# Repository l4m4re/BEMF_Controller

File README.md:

# BEMF Controller

The Back EMF Controller is an experimental evolution of the successful [EasyController3](https://github.com/pgrady3/EasyController3). 

This version incorporates an asymmetric bridge topology, which allows for capturing and reusing the energy from the motor's back EMF, which is normally wasted because of the use of freewheeling diodes.

This allows for a more efficient controller, and potentially a longer range for battery-powered applications, as explained on [Wikipedia](https://en.wikipedia.org/wiki/Switched_reluctance_motor#Power_circuitry):

> The phases in an asymmetric bridge converter correspond to the motor phases. If both of the power switches on either side of the phase are turned on, then that corresponding phase is actuated. Once the current has risen above the set value, the switch turns off. The energy now stored within the winding maintains the current in the same direction, the so-called back EMF (BEMF). This BEMF is fed back through the diodes to the capacitor for re-use, thus improving efficiency.

In addition to this, the capacitor that is used to store the energy from the back EMF is implemented in a bank of 4 capacitors, which are switched between series (BEMF capture) and parallel (coil energizing) by means of a couple of diodes:

[Spice simulations](http://tuks.nl/wiki/index.php/Main/BEMFRecoveryCircuit) have shown that this way the time needed to collapse the magnetic field in the motor is significantly reduced, which might help to reduce rotor drag and thus further improve the efficiency of the controller:

At this moment, all of this is still a work in progress, and the controller is still in the design phase. 

## Schematic

At this moment, the schematic is being developed using KiCad, and can be found in the `kicad` folder. The schematic is still a work in progress, but the current version can be found [here](/kicad/BEMF_controller.pdf).

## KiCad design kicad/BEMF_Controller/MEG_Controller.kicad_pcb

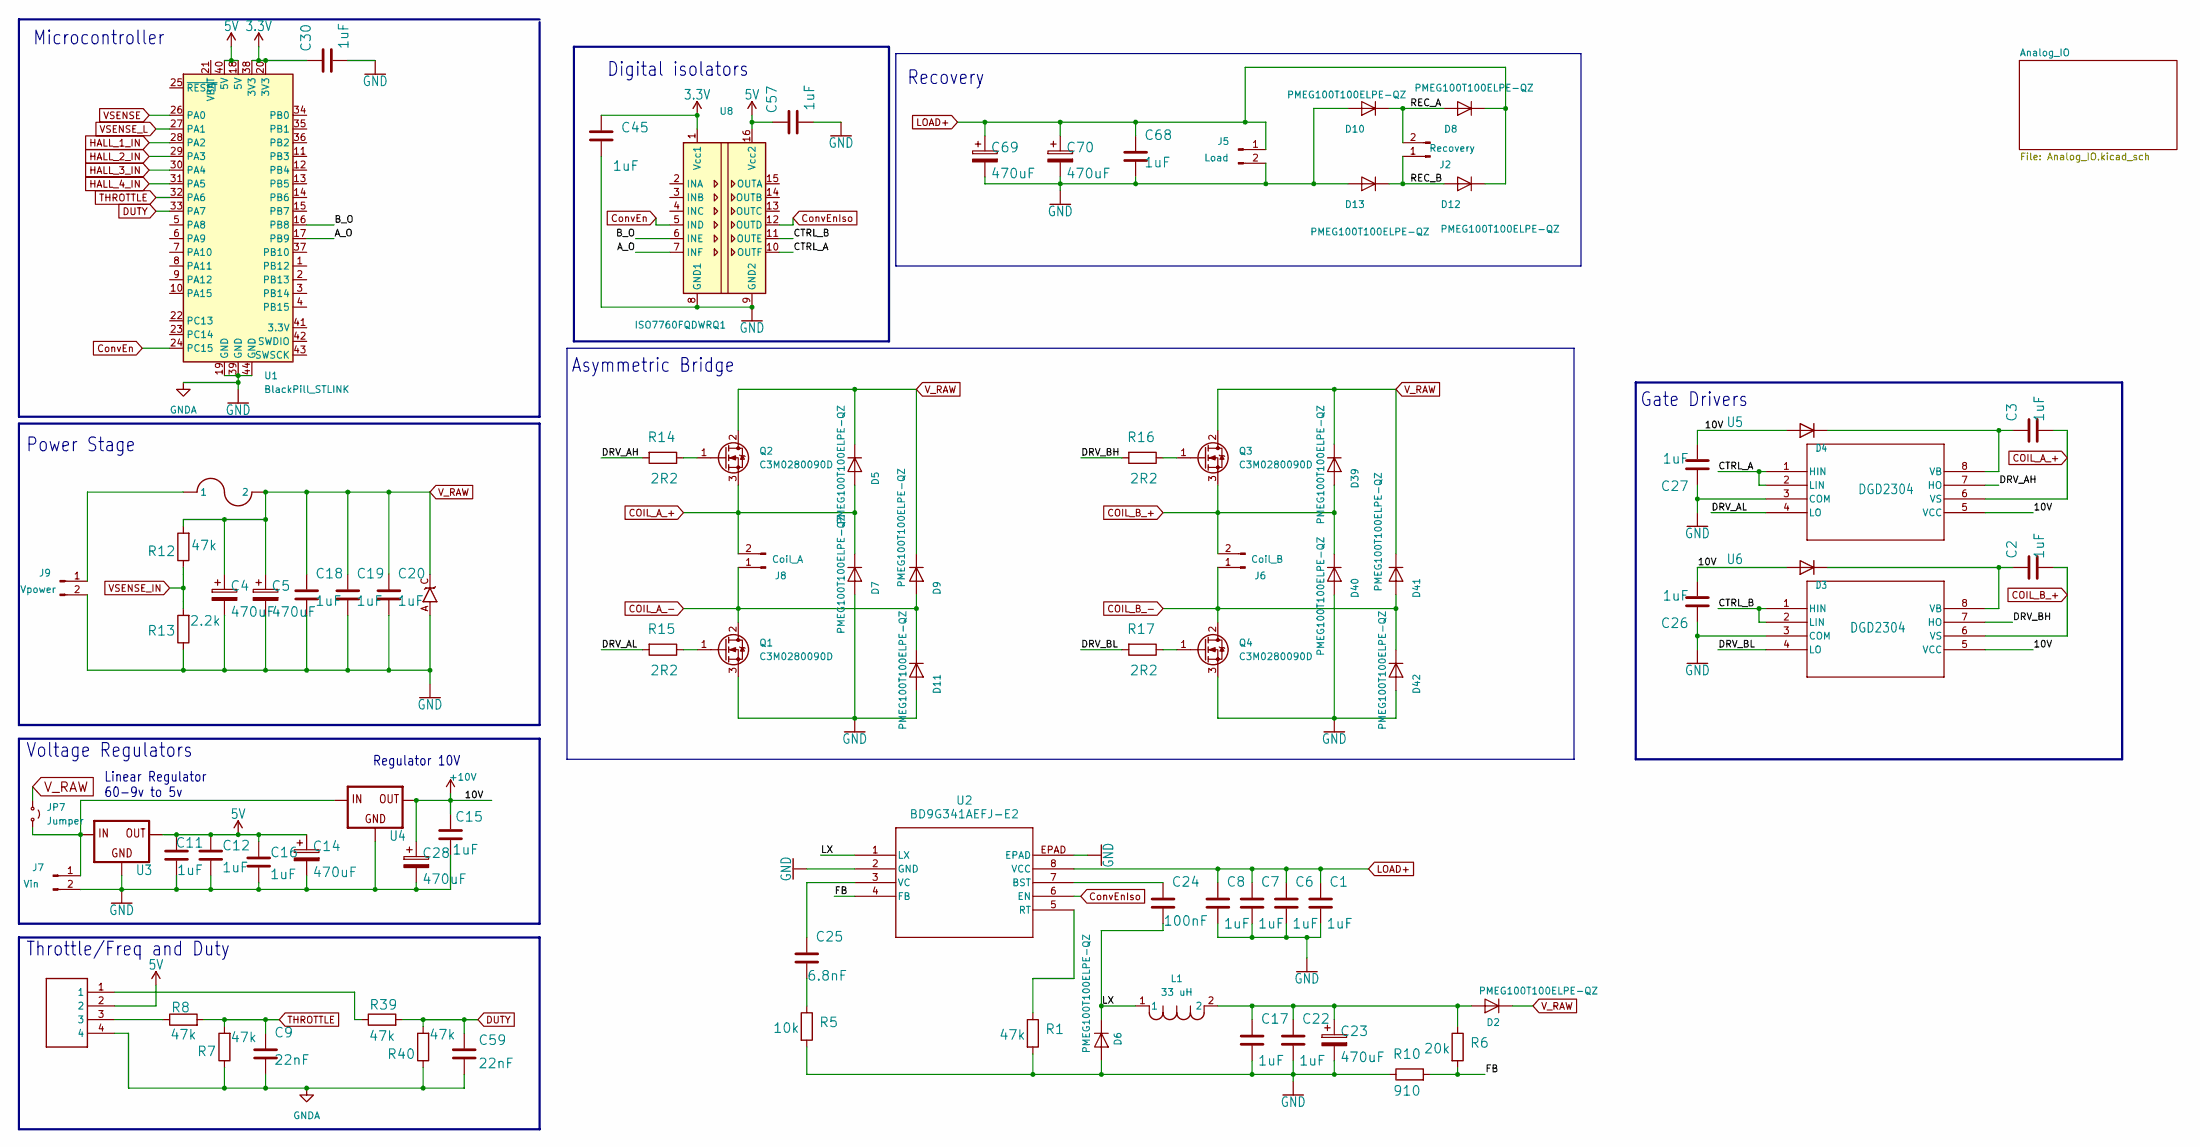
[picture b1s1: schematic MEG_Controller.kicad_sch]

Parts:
C1, C2, C3, C6, C7, C8, C11, C12, C15, C16, C17, C18, C19, C20, C22, C26, C27, C30, C45, C57, C68: 1uF; C_1812_4532Metric
C4, C5, C14, C23, C28, C69, C70: 470uF; CP_Radial_D10.0mm_P5.00mm
C9, C59: 22nF; C_0805_2012Metric
C24: 100nF; C_0805_2012Metric
C25: 6.8nF; C_0805_2012Metric
D1: TVS_UNIDO-214AC; DO-214AC
D2, D5, D6, D7, D8, D9, D10, D11, D12, D13, D39, D40, D41, D42: PMEG100T100ELPE-QZ; Nexperia_CFP15_SOT-1289
D3, D4: SMD-DIODE-100V-200MA(SOD-123); D_SOD-123
J1: HEADER4VALULOK; TerminalBlock_Phoenix_MKDS-1,5-4-5.08_1x04_P5.08mm_Horizont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
J2: Recovery; TerminalBlock_Phoenix_MKDS-1,5-2-5.08_1x02_P5.08mm_Horizont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
J3: FUSE; AUTO_FUSE
J5: Load; TerminalBlock_Phoenix_MKDS-1,5-2-5.08_1x02_P5.08mm_Horizont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
J6: Coil_B; TerminalBlock_Phoenix_MKDS-1,5-2-5.08_1x02_P5.08mm_Horizont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
J7: Vin; TerminalBlock_Phoenix_MKDS-1,5-2-5.08_1x02_P5.08mm_Horizont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
J8: Coil_A; TerminalBlock_Phoenix_MKDS-1,5-2-5.08_1x02_P5.08mm_Horizont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
J9: Vpower; TerminalBlock_Phoenix_MKDS-1,5-2-5.08_1x02_P5.08mm_Horizont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
JP7: Jumper; SolderJumper-2_P1.3mm_Open_RoundedPad1.0x1.5mm
L1: 33 uH; IND_BOURNS_SRN1060
Q1, Q2, Q3, Q4: C3M0280090D; TO-247-3_Vertical
R1, R7, R8, R12, R39, R40: 47k; R_1206_3216Metric
R5: 10k; R_1206_3216Metric
R6: 20k; R_1206_3216Metric
R10: 910; R_1206_3216Metric
R13: 2.2k; R_1206_3216Metric
R14, R15, R16, R17: 2R2; R_1206_3216Metric
U1: BlackPill_STLINK
U2: BD9G341AEFJ-E2; HTSOP-J8_ROM
U3: V_REG_7805; V78W_BACKWARDS
U4: V_REG_7810; V78W_BACKWARDS
U5, U6: DGD2304; SOICN-8_LTF
U8: ISO7760FQDWRQ1; SOIC-16W_7.5x10.3mm_P1.27mm

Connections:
3.3V: C30.1, C45.1, U1.20 (3V3), U1.38 (3V3), U8.1 (Vcc1); also elsewhere on the board
5V: C11.1, C12.1, C14.1, C16.1, C57.1, J1.2, U1.18 (5V), U1.40 (5V), U3.OUT, U8.16 (Vcc2); also elsewhere on the board
+10V: C15.1, C26.2, C27.2, C28.1, D3.2 (A), D4.2 (A), U4.OUT, U5.5 (VCC), U6.5 (VCC)
/A_O: U1.17 (PB9), U8.7 (INF)
/B_O: U1.16 (PB8), U8.6 (INE)
/CTRL_A: U5.1 (HIN), U5.2 (LIN), U8.10 (OUTF)
/CTRL_B: U6.1 (HIN), U6.2 (LIN), U8.11 (OUTE)
/DRV_AH: R14.2, U5.7 (HO)
/DRV_AL: R15.2, U5.4 (LO)
/DRV_BH: R16.2, U6.7 (HO)
/DRV_BL: R17.2, U6.4 (LO)
/FB: R6.2, R10.2, U2.4 (FB)
/LX: C24.2, D6.1 (A), D6.2 (A), L1.1, U2.1 (LX)
/REC_A: D8.3 (K), D10.1 (A), D10.2 (A), J2.2
/REC_B: D12.3 (K), D13.1 (A), D13.2 (A), J2.1
COIL_A_+: C3.2, D5.3 (K), D7.1 (A), D7.2 (A), J8.2, Q2.3 (S), U5.6 (VS)
COIL_A_-: D9.3 (K), D11.1 (A), D11.2 (A), J8.1, Q1.2 (D)
COIL_B_+: C2.2, D39.3 (K), D40.1 (A), D40.2 (A), J6.2, Q3.3 (S), U6.6 (VS)
COIL_B_-: D41.3 (K), D42.1 (A), D42.2 (A), J6.1, Q4.2 (D)
ConvEn: U1.24 (PC15), U8.5 (IND)
ConvEnIso: U2.6 (EN), U8.12 (OUTD)
DUTY: C59.1, R39.2, R40.2, U1.33 (PA7)
GND: C1.2, C4.2, C5.2, C6.2, C7.2, C8.2, C9.2, C11.2, C12.2, C14.2, C15.2, C16.2, C17.2, C18.2, C19.2, C20.2, C22.2, C23.2, C26.1, C27.1, C28.2, C30.2, C45.2, C57.2, C59.2, C68.2, C69.2, C70.2, D1.A, D6.3 (K), D7.3 (K), D10.3 (K), D11.3 (K), D13.3 (K), D40.3 (K), D42.3 (K), J1.4, J5.2, J7.2, J9.2, Q1.3 (S), Q4.3 (S), R1.2, R5.2, R7.1, R10.1, R13.1, R40.1, U1.19 (GND), U1.39 (GND), U1.44 (GND), U2.2 (GND), U2.EPAD, U3.GND, U4.GND, U5.3 (COM), U6.3 (COM), U8.8 (GND1), U8.9 (GND2); also elsewhere on the board
HALL_1_IN: U1.28 (PA2); also elsewhere on the board
HALL_2_IN: U1.29 (PA3); also elsewhere on the board
HALL_3_IN: U1.30 (PA4); also elsewhere on the board
HALL_4_IN: U1.31 (PA5); also elsewhere on the board
LOAD+: C1.1, C6.1, C7.1, C8.1, C68.1, C69.1, C70.1, D8.1 (A), D8.2 (A), D12.1 (A), D12.2 (A), J5.1, U2.8 (VCC); also elsewhere on the board
unnamed: C25.2, R5.1
unnamed: C17.1, C22.1, C23.1, D2.3 (K), L1.2, R6.1
unnamed: C2.1, D3.1 (K), U6.8 (VB)
unnamed: C3.1, D4.1 (K), U5.8 (VB)
unnamed: J1.1, R39.1
unnamed: J1.3, R8.1
unnamed: J7.1, JP7.2 (B), U3.IN, U4.IN
unnamed: J3.1A (1), J3.1B (1), J9.1
unnamed: Q1.1 (G), R15.1
unnamed: Q2.1 (G), R14.1
unnamed: Q3.1 (G), R16.1
unnamed: Q4.1 (G), R17.1
unnamed: C24.1, U2.7 (BST)
unnamed: R1.1, U2.5 (RT)
unnamed: C25.1, U2.3 (VC)
THROTTLE: C9.1, R7.2, R8.2, U1.32 (PA6)
VSENSE: U1.26 (PA0); also elsewhere on the board
VSENSE_IN: R12.1, R13.2; also elsewhere on the board
VSENSE_L: U1.27 (PA1); also elsewhere on the board
V_RAW: C4.1, C5.1, C18.1, C19.1, C20.1, D1.C, D2.1 (A), D2.2 (A), D5.1 (A), D5.2 (A), D9.1 (A), D9.2 (A), D39.1 (A), D39.2 (A), D41.1 (A), D41.2 (A), J3.2A (2), J3.2B (2), JP7.1 (A), Q2.2 (D), Q3.2 (D), R12.2

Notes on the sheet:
Digital isolators
Power Stage
Throttle/Freq and Duty
Microcontroller
Regulator 10V
Linear Regulator 60-9v to 5v
Voltage Regulators
Gate Drivers
Recovery
Asymmetric Bridge

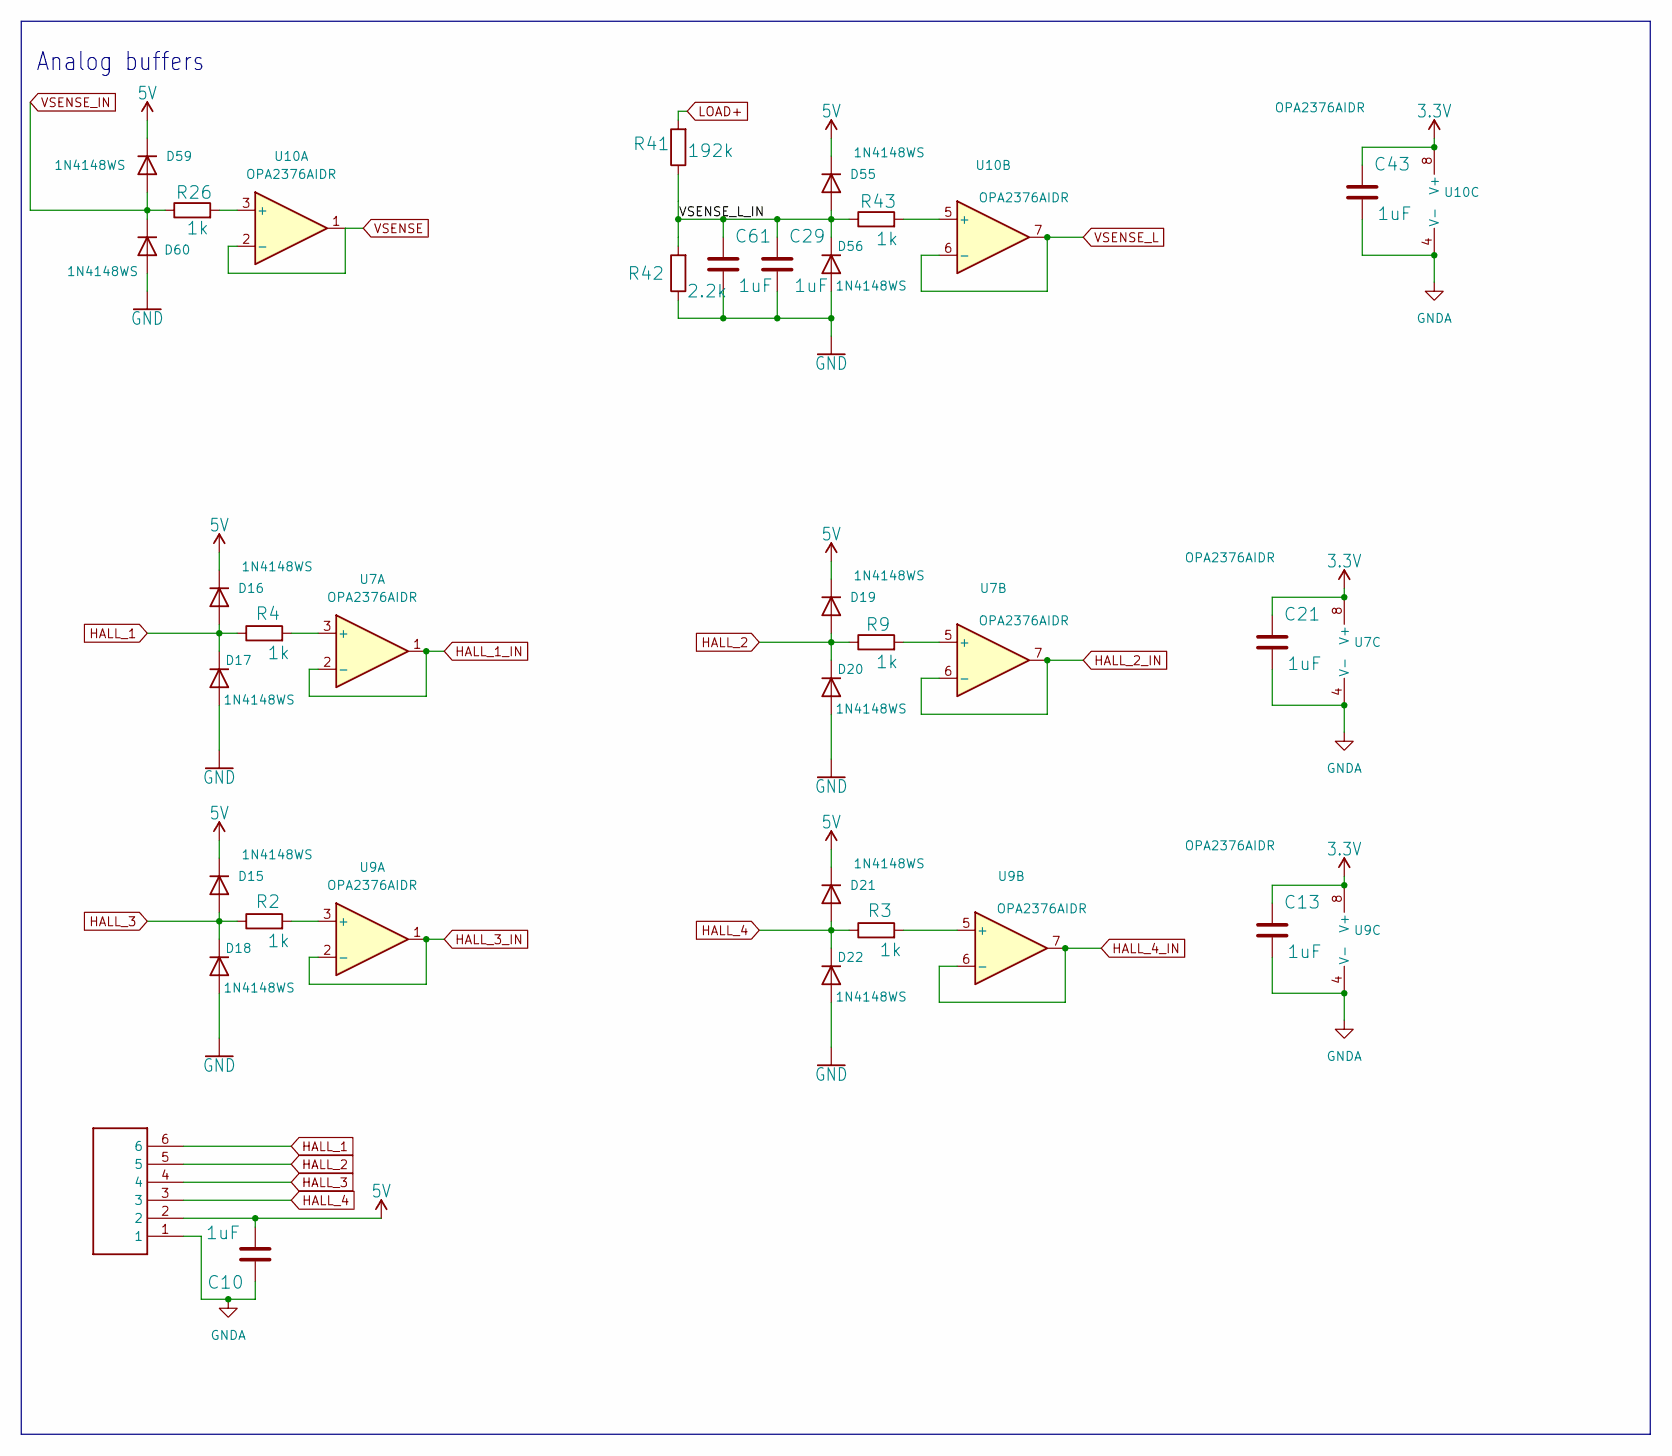
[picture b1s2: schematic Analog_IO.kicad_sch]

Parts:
C10, C13, C21, C29, C43, C61: 1uF; C_1812_4532Metric
D15, D16, D17, D18, D19, D20, D21, D22, D55, D56, D59, D60: 1N4148WS; D_SOD-323
J4: HEADER6; TerminalBlock_Phoenix_MKDS-1,5-6_1x06_P5.00mm_Horizontal
R2, R3, R4, R9, R26, R43: 1k; R_1206_3216Metric
R41: 192k; R_1206_3216Metric
R42: 2.2k; R_1206_3216Metric
U7, U9, U10: OPA2376AIDR; D8

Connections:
3.3V: C13.1, C21.1, C43.1, U7.8 (V+), U9.8 (V+), U10.8 (V+); also elsewhere on the board
5V: C10.2, D15.1 (K), D16.1 (K), D19.1 (K), D21.1 (K), D55.1 (K), D59.1 (K), J4.2; also elsewhere on the board
/Analog_IO/VSENSE_L_IN: C29.1, C61.1, D55.2 (A), D56.1 (K), R41.1, R42.2, R43.1
GND: C10.1, C13.2, C21.2, C29.2, C43.2, C61.2, D17.2 (A), D18.2 (A), D20.2 (A), D22.2 (A), D56.2 (A), D60.2 (A), J4.1, R42.1, U7.4 (V-), U9.4 (V-), U10.4 (V-); also elsewhere on the board
HALL_1: D16.2 (A), D17.1 (K), J4.6, R4.1
HALL_1_IN: U7.1, U7.2 (-); also elsewhere on the board
HALL_2: D19.2 (A), D20.1 (K), J4.5, R9.1
HALL_2_IN: U7.6 (-), U7.7; also elsewhere on the board
HALL_3: D15.2 (A), D18.1 (K), J4.4, R2.1
HALL_3_IN: U9.1, U9.2 (-); also elsewhere on the board
HALL_4: D21.2 (A), D22.1 (K), J4.3, R3.1
HALL_4_IN: U9.6 (-), U9.7; also elsewhere on the board
LOAD+: R41.2; also elsewhere on the board
unnamed: R4.2, U7.3 (+)
unnamed: R9.2, U7.5 (+)
unnamed: R2.2, U9.3 (+)
unnamed: R3.2, U9.5 (+)
unnamed: R26.2, U10.3 (+)
unnamed: R43.2, U10.5 (+)
VSENSE: U10.1, U10.2 (-); also elsewhere on the board
VSENSE_IN: D59.2 (A), D60.1 (K), R26.1; also elsewhere on the board
VSENSE_L: U10.6 (-), U10.7; also elsewhere on the board

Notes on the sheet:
Analog buffers

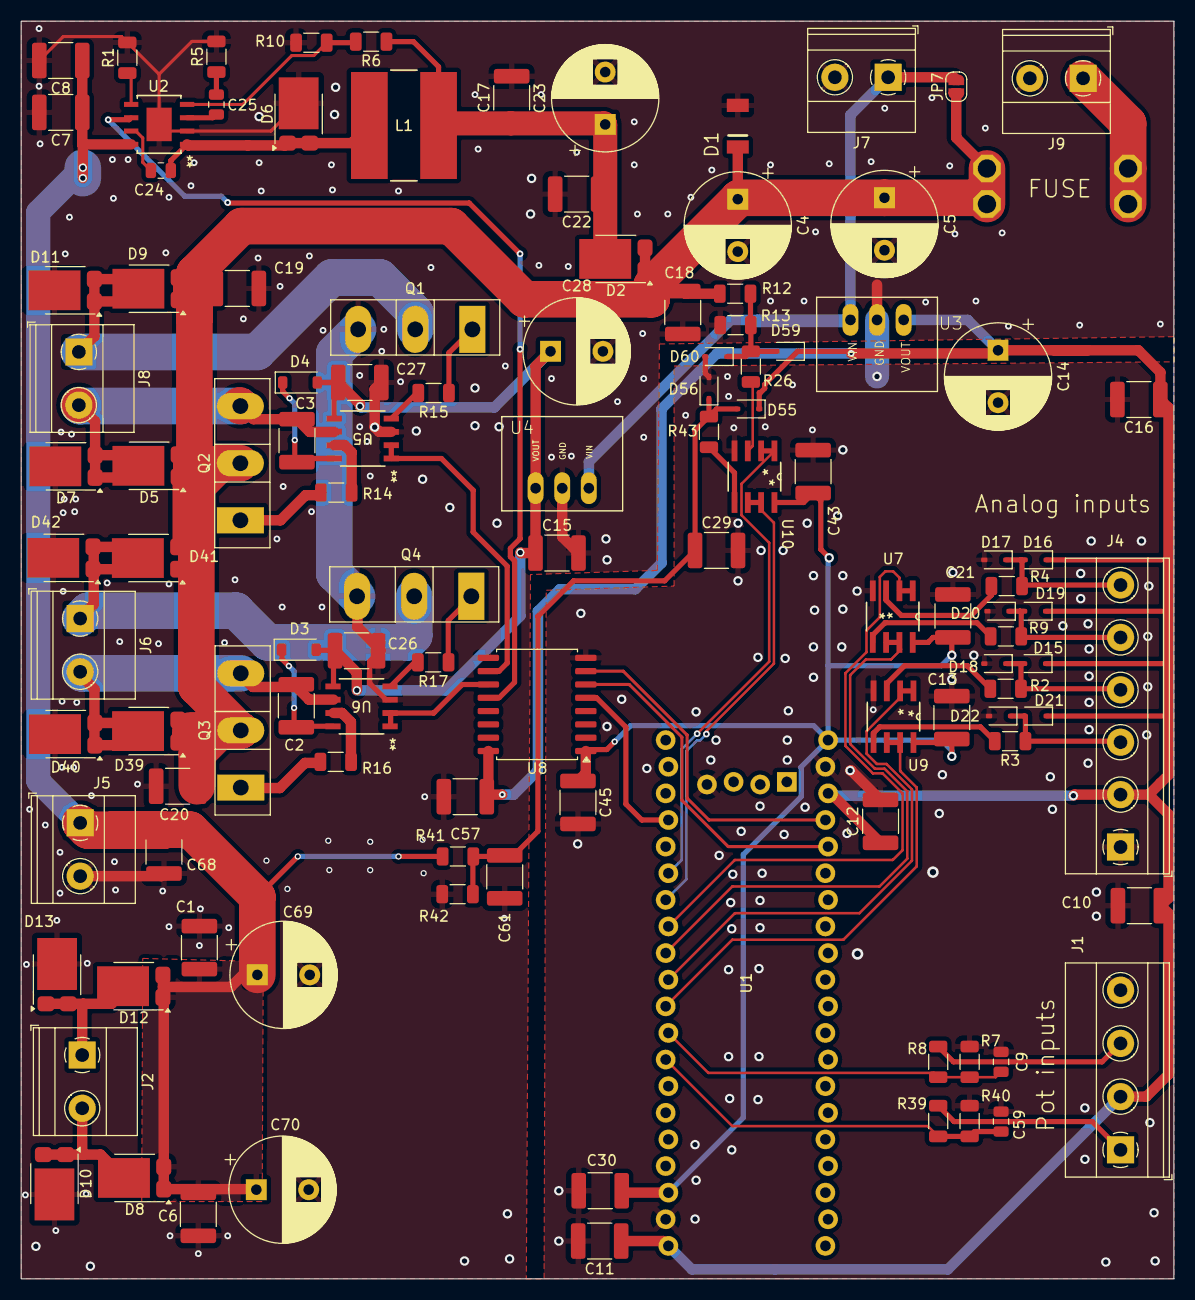
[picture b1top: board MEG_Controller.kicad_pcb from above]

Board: 2 copper layers, 110.0 x 120.0 mm, 114 parts (0 on the bottom side), 59 nets.

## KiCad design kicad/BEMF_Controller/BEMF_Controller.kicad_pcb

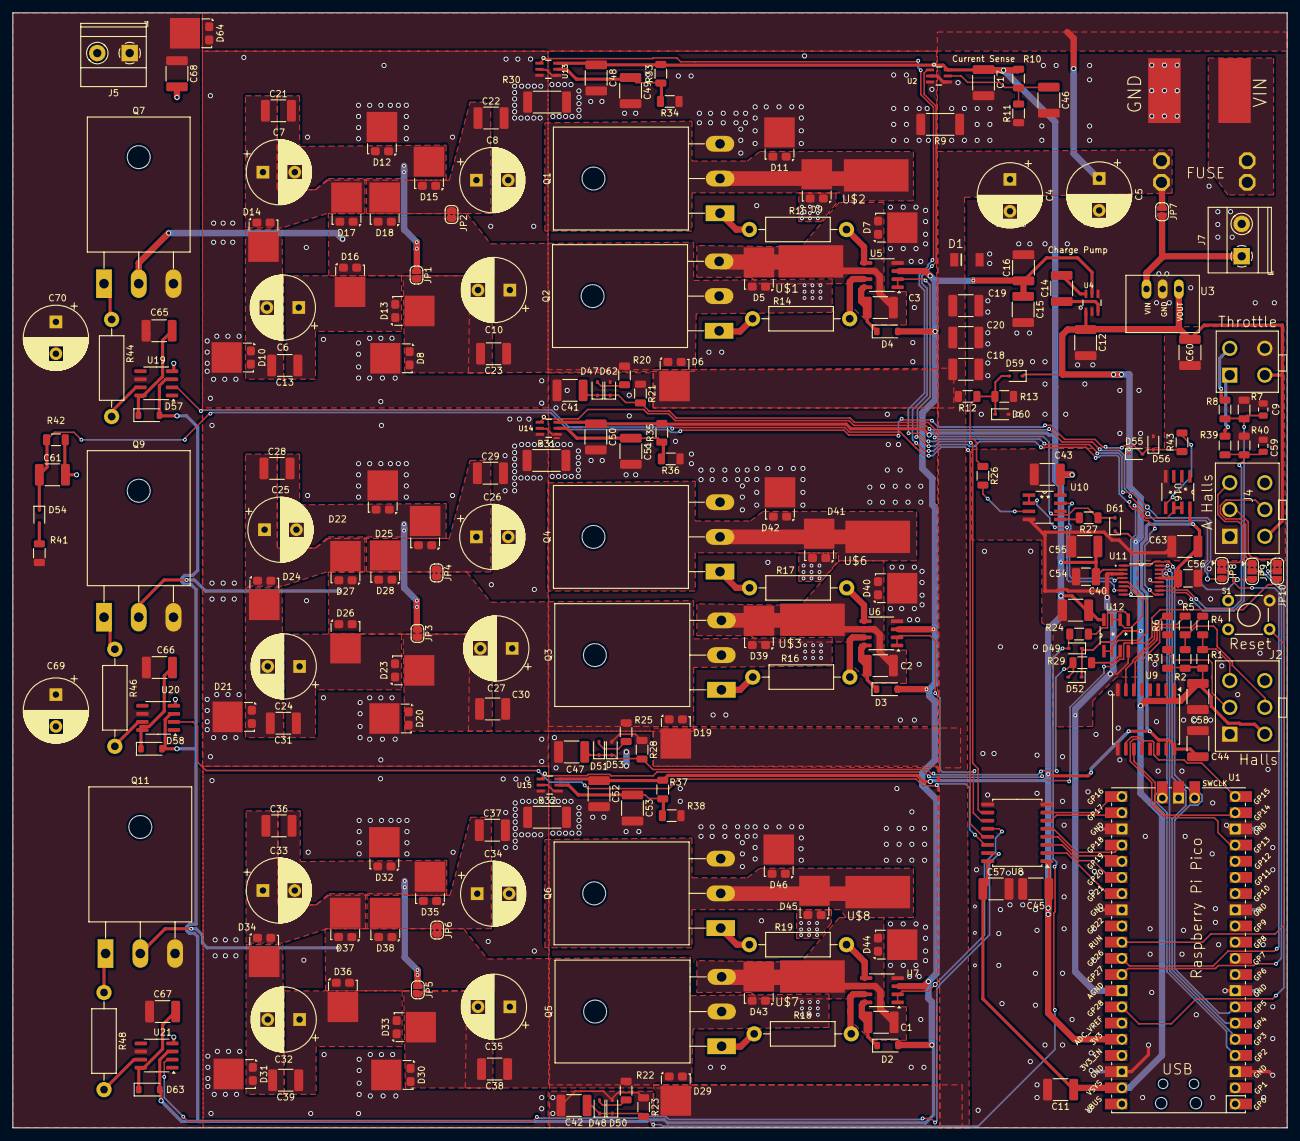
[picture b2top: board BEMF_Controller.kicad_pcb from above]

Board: 2 copper layers, 200.0 x 175.0 mm, 231 parts (0 on the bottom side), 129 nets.

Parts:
C1, C2, C3, C11, C12, C13, C14, C15, C16, C17, C18, C19, C20, C21, C22, C23, C28, C29, C30, C31, C36, C37, C38, C39, C40, C41, C42, C43, C44, C45, C46, C47, C48, C49, C50, C51, C52, C53, C54, C57, C58, C60, C61, C63, C65, C66, C67, C68: 1uF; C_1812_4532Metric
C4, C5, C6, C7, C8, C10, C24, C25, C26, C27, C32, C33, C34, C35, C69, C70: 470uF; CP_Radial_D10.0mm_P5.00mm
C9, C59: 22nF; C_0805_2012Metric
C55, C56: 100nF; C_1210_3225Metric_Pad1.33x2.70mm_HandSolder
D1: TVS_UNIDO-214AC; DO-214AC
D2, D3, D4, D57, D58, D63: SMD-DIODE-100V-200MA(SOD-123); D_SOD-123
D5, D6, D7, D8, D9, D10, D11, D12, D13, D14, D15, D16, D17, D18, D19, D20, D21, D22, D23, D24, D25, D26, D27, D28, D29, D30, D31, D32, D33, D34, D35, D36, D37, D38, D39, D40, D41, D42, D43, D44, D45, D46, D64: FSV20150V; TO-277A
D47, D48, D49, D50, D51, D52, D53, D54, D55, D56, D59, D60, D61, D62: 1N4148WS; D_SOD-323
J1: HEADER4VALULOK; 4PINVALULOK
J2, J4: HEADER6; 6PINVALULOK
J3: FUSE; AUTO_FUSE
J5: Load; TerminalBlock_Phoenix_MKDS-1,5-2-5.08_1x02_P5.08mm_Horizont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
J7: Vin; TerminalBlock_Phoenix_MKDS-1,5-2-5.08_1x02_P5.08mm_Horizont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
JP1, JP3, JP5, JP7: Jumper; SolderJumper-2_P1.3mm_Open_RoundedPad1.0x1.5mm
JP2, JP4, JP6: Jumper; SolderJumper-2_P1.3mm_Bridged2Bar_RoundedPad1.0x1.5mm
JP8, JP9, JP10: SolderJumper_3_Bridged12; SolderJumper-3_P1.3mm_Bridged2Bar12_RoundedPad1.0x1.5mm
Q1, Q2, Q3, Q4, Q5, Q6, Q7, Q9, Q11: C3M0280090D; TO-247-3_Horizontal_TabDown
R1, R2, R3, R4, R5, R6, R13, R21, R23, R28, R42: 2.2k; R_1206_3216Metric
R7, R8, R10, R11, R12, R33, R34, R35, R36, R37, R38, R39, R40: 47k; R_1206_3216Metric
R9, R30, R31, R32: 0.0005; R_2512_6332Metric_Pad1.40x3.35mm_HandSolder
R14, R15, R16, R17, R18, R19, R44, R46, R48: 10; R_Axial_DIN0411_L9.9mm_D3.6mm_P15.24mm_Horizontal
R20, R22, R25, R41: 192k; R_1206_3216Metric
R24, R26, R27, R29, R43: 1k; R_1206_3216Metric
S1: MOMENTARY-SWITCH-SPST-PTH-6.0MM; TACTILE_SWITCH_PTH_6.0MM
U1: Raspberry Pi Pico; RPi_Pico_SMD_TH
U2, U13, U14, U15: INA181; SOT23-6
U3: V_REG_78XX; V78W_BACKWARDS
U4: TC1240A; SOT23-6
U5, U6, U7, U19, U20, U21: DGD2304; SOIC-8_3.9x4.9mm_P1.27mm
U8, U9: ISO7760FQDWRQ1; SOIC-16W_7.5x10.3mm_P1.27mm
U10, U12, U16: OPA2376AIDR; D8
U11: ADC108S022CIMTX/NOPB; MTC16
U$1: COIL_A+; PAD
U$2, U$3, U$4, U$5, U$6, U$7, U$8: PAD

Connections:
3.3V: C17.1, C40.1, C43.1, C44.1, C45.1, C48.1, C50.1, C52.1, C54.1, C55.1, C56.1, C63.1, R10.2, R33.2, R35.2, R37.2, U1.36 (3V3), U2.6 (VCC), U8.1 (Vcc1), U9.16 (Vcc2), U10.8 (V+), U11.2 (VA), U11.13 (VD), U12.8 (V+), U13.6 (VCC), U14.6 (VCC), U15.6 (VCC), U16.8 (V+)
5V: C11.1, C12.1, C57.1, C58.1, C60.2, D49.1 (K), D52.1 (K), D55.1 (K), D59.1 (K), D61.1 (K), J1.2, J2.2, J4.2, R1.2, R2.2, R3.2, U1.39 (VSYS), U3.OUT, U4.1 (VIN), U8.16 (Vcc2), U9.1 (Vcc1)
/10V: C15.1, C16.1, D2.2 (A), D3.2 (A), D4.2 (A), D57.2 (A), D58.2 (A), D63.2 (A), U4.5 (VOUT), U5.3 (VCC), U6.3 (VCC), U7.3 (VCC), U19.3 (VCC), U20.3 (VCC), U21.3 (VCC)
/A_O: U1.21 (GPIO16), U8.7 (INF)
/Analog_IO/VSENSE_A_IN: C41.1, D47.1 (K), D61.2 (A), D62.1 (K), R21.2, R27.1
/Analog_IO/VSENSE_B_IN: C47.1, D51.1 (K), D52.2 (A), D53.1 (K), R28.2, R29.1
/Analog_IO/VSENSE_C_IN: C42.1, D48.1 (K), D49.2 (A), D50.1 (K), R23.2, R24.1
/Analog_IO/VSENSE_L_IN: C61.1, D54.1 (K), D55.2 (A), D56.1 (K), R42.2, R43.1
/B_O: U1.22 (GPIO17), U8.6 (INE)
/CTRL_A: U5.1 (LIN), U5.2 (HIN), U8.10 (OUTF)
/CTRL_B: U6.1 (LIN), U6.2 (HIN), U8.11 (OUTE)
/CTRL_C: U7.1 (LIN), U7.2 (HIN), U8.12 (OUTD)
/CTRL_DA: U8.13 (OUTC), U19.2 (HIN)
/CTRL_DB: U8.14 (OUTB), U20.2 (HIN)
/CTRL_DC: U8.15 (OUTA), U21.2 (HIN)
/C_O: U1.24 (GPIO18), U8.5 (IND)
/DA_O: U1.25 (GPIO19), U8.4 (INC)
/DB_O: U1.26 (GPIO20), U8.3 (INB)
/DCH_A_H: R44.2, U19.7 (HO)
/DCH_B_H: R46.2, U20.7 (HO)
/DCH_C_H: R48.2, U21.7 (HO)
/DC_O: U1.27 (GPIO21), U8.2 (INA)
/DRV_AH: R14.2, U5.7 (HO)
/DRV_AL: R15.2, U5.5 (LO)
/DRV_BH: R16.2, U6.7 (HO)
/DRV_BL: R17.2, U6.5 (LO)
/DRV_CH: R18.2, U7.7 (HO)
/DRV_CL: R19.2, U7.5 (LO)
/HA_I: U1.17 (GPIO13), U9.12 (OUTD)
/HB_I: U1.19 (GPIO14), U9.11 (OUTE)
/HC_I: U1.20 (GPIO15), U9.10 (OUTF)
CAP_BANK_A+: C10.1, C23.1, D5.1 (A), D5.2 (A), D6.1 (A), D6.2 (A), D9.1 (A), D9.2 (A), D16.1 (A), D16.2 (A), D17.1 (A), D17.2 (A), D18.1 (A), D18.2 (A), JP2.2 (B), Q2.2 (D), Q7.2 (D), R20.2
CAP_BANK_B+: C27.1, C30.1, D19.1 (A), D19.2 (A), D26.1 (A), D26.2 (A), D27.1 (A), D27.2 (A), D28.1 (A), D28.2 (A), D39.1 (A), D39.2 (A), D41.1 (A), D41.2 (A), JP4.2 (B), Q3.2 (D), Q9.2 (D), R25.2
CAP_BANK_C+: C35.1, C38.1, D29.1 (A), D29.2 (A), D36.1 (A), D36.2 (A), D37.1 (A), D37.2 (A), D38.1 (A), D38.2 (A), D43.1 (A), D43.2 (A), D45.1 (A), D45.2 (A), JP6.2 (B), Q5.2 (D), Q11.2 (D), R22.2
CAP_BANK_GND: C41.2, C42.2, C47.2, C48.2, C49.2, C50.2, C51.2, C52.2, C53.2, D7.3 (K), D11.3 (K), D40.3 (K), D42.3 (K), D44.3 (K), D46.3 (K), D50.2 (A), D53.2 (A), D62.2 (A), Q1.3 (S), Q4.3 (S), Q6.3 (S), R9.2, R21.1, R23.1, R28.1, R30.2, R31.2, R32.2, R34.1, R36.1, R38.1, U2.3 (IN+), U5.4 (GND), U6.4 (GND), U7.4 (GND), U13.2 (GND), U13.4 (IN-), U14.2 (GND), U14.4 (IN-), U15.2 (GND), U15.4 (IN-)
COIL_A_+: C3.2, D5.3 (K), D7.1 (A), D7.2 (A), Q2.3 (S), U5.6 (VS), U$1.PAD
COIL_A_-: D9.3 (K), D11.1 (A), D11.2 (A), Q1.2 (D), U$2.PAD
COIL_B_+: C2.2, D39.3 (K), D40.1 (A), D40.2 (A), Q3.3 (S), U6.6 (VS), U$3.PAD
COIL_B_-: D41.3 (K), D42.1 (A), D42.2 (A), Q4.2 (D), U$6.PAD
COIL_C_+: C1.2, D43.3 (K), D44.1 (A), D44.2 (A), Q5.3 (S), U7.6 (VS), U$7.PAD
COIL_C_-: D45.3 (K), D46.1 (A), D46.2 (A), Q6.2 (D), U$8.PAD
DUTY: C59.1, R39.2, R40.2, U11.11 (IN7)
GND: C4.2, C5.2, C11.2, C12.2, C15.2, C16.2, C17.2, C18.2, C19.2, C20.2, C44.2, C45.2, C46.2, C56.2, C57.2, C58.2, C61.2, C68.2, C69.2, C70.2, D1.A, D56.2 (A), D60.2 (A), J2.1, J5.2, J7.2, R9.1, R11.1, R13.1, R42.1, S1.3 (2), U1.3 (GND), U1.8 (GND), U1.13 (GND), U1.18 (GND), U1.23 (GND), U1.28 (GND), U1.38 (GND), U1.42 (GND), U2.2 (GND), U2.4 (IN-), U3.GND, U4.2 (GND), U4.4 (SHDN), U8.8 (GND1), U8.9 (GND2), U9.8 (GND1), U9.9 (GND2), U11.12 (DGND), U19.4 (GND), U20.4 (GND), U21.4 (GND), U$5.PAD
GNDA: C9.2, C40.2, C43.2, C54.2, C55.2, C59.2, C60.1, C63.2, J1.4, J4.1, R7.1, R40.1, U1.33 (AGND), U10.4 (V-), U11.3 (AGND), U12.4 (V-), U16.4 (V-)
HALL_1: J4.5, JP8.1 (A)
HALL_2: J4.4, JP9.1 (A)
HALL_3: J4.3, JP10.1 (A)
HALL_A: R4.2, U9.5 (IND)
HALL_B: R5.2, U9.6 (INE)
HALL_C: R6.2, U9.7 (INF)
ISENSE: U2.1 (OUT), U11.9 (IN5)
ISENSE_A: JP8.3 (B), U13.1 (OUT)
ISENSE_A_HALL_1: JP8.2 (C), U1.31 (GPIO26_ADC0)
ISENSE_B: JP9.3 (B), U14.1 (OUT)
ISENSE_B_HALL_2: JP9.2 (C), U1.32 (GPIO27_ADC1)
ISENSE_C: JP10.3 (B), U15.1 (OUT)
ISENSE_C_HALL_3: JP10.2 (C), U1.34 (GPIO28_ADC2)
LOAD+: C65.2, C66.2, C67.2, C68.1, C69.1, C70.1, D64.3 (K), J5.1, Q7.3 (S), Q9.3 (S), Q11.3 (S), R41.2, U19.6 (VS), U20.6 (VS), U21.6 (VS)
unnamed: C1.1, D2.1 (K), U7.8 (VB)
unnamed: C2.1, D3.1 (K), U6.8 (VB)
unnamed: C3.1, D4.1 (K), U5.8 (VB)
unnamed: C10.2, C23.2, D8.1 (A), D8.2 (A), D13.3 (K), JP1.2 (B)
unnamed: C6.2, C13.2, D10.1 (A), D10.2 (A), D14.3 (K)
unnamed: C7.2, C21.2, D12.1 (A), D12.2 (A), D15.3 (K), JP1.1 (A)
unnamed: C6.1, C13.1, D13.1 (A), D13.2 (A), D16.3 (K)
unnamed: C7.1, C21.1, D14.1 (A), D14.2 (A), D17.3 (K)
unnamed: C8.1, C22.1, D15.1 (A), D15.2 (A), D18.3 (K), JP2.1 (A)
unnamed: C27.2, C30.2, D20.1 (A), D20.2 (A), D23.3 (K), JP3.2 (B)
unnamed: C24.2, C31.2, D21.1 (A), D21.2 (A), D24.3 (K)
unnamed: C25.2, C28.2, D22.1 (A), D22.2 (A), D25.3 (K), JP3.1 (A)
unnamed: C24.1, C31.1, D23.1 (A), D23.2 (A), D26.3 (K)
unnamed: C25.1, C28.1, D24.1 (A), D24.2 (A), D27.3 (K)
unnamed: C26.1, C29.1, D25.1 (A), D25.2 (A), D28.3 (K), JP4.1 (A)
unnamed: C35.2, C38.2, D30.1 (A), D30.2 (A), D33.3 (K), JP5.2 (B)
unnamed: C32.2, C39.2, D31.1 (A), D31.2 (A), D34.3 (K)
unnamed: C33.2, C36.2, D32.1 (A), D32.2 (A), D35.3 (K), JP5.1 (A)
unnamed: C32.1, C39.1, D33.1 (A), D33.2 (A), D36.3 (K)
unnamed: C33.1, C36.1, D34.1 (A), D34.2 (A), D37.3 (K)
unnamed: C34.1, C37.1, D35.1 (A), D35.2 (A), D38.3 (K), JP6.1 (A)
unnamed: D47.2 (A), R20.1
unnamed: D48.2 (A), R22.1
unnamed: D51.2 (A), R25.1
unnamed: D54.2 (A), R41.1
unnamed: C65.1, D57.1 (K), U19.8 (VB)
unnamed: C66.1, D58.1 (K), U20.8 (VB)
unnamed: C67.1, D63.1 (K), U21.8 (VB)
unnamed: J1.1, R39.1
unnamed: J1.3, R8.1
unnamed: J2.3, R3.1, R6.1
unnamed: J2.4, R2.1, R5.1
unnamed: J2.5, R1.1, R4.1
unnamed: J3.1A (1), J3.1B (1), U$4.PAD
unnamed: J7.1, JP7.2 (B), U3.IN
unnamed: Q1.1 (G), R15.1
unnamed: Q2.1 (G), R14.1
unnamed: Q3.1 (G), R16.1
unnamed: Q4.1 (G), R17.1
unnamed: Q5.1 (G), R18.1
unnamed: Q6.1 (G), R19.1
unnamed: Q7.1 (G), R44.1
unnamed: Q9.1 (G), R46.1
unnamed: Q11.1 (G), R48.1
unnamed: S1.1, U1.30 (RUN)
unnamed: C46.1, R10.1, R11.2, U2.5 (REF)
unnamed: C14.2, U4.6 (C+)
unnamed: C14.1, U4.3 (C-)
unnamed: R26.2, U10.3 (+)
unnamed: R27.2, U10.5 (+)
unnamed: R29.2, U12.3 (+)
unnamed: R24.2, U12.5 (+)
unnamed: C49.1, R33.1, R34.2, U13.5 (REF)
unnamed: C51.1, R35.1, R36.2, U14.5 (REF)
unnamed: C53.1, R37.1, R38.2, U15.5 (REF)
unnamed: R43.2, U16.5 (+)
SHUNT_A+: C8.2, C22.2, D8.3 (K), D10.3 (K), D12.3 (K), R30.1, U13.3 (IN+)
SHUNT_B+: C26.2, C29.2, D20.3 (K), D21.3 (K), D22.3 (K), R31.1, U14.3 (IN+)
SHUNT_C+: C34.2, C37.2, D30.3 (K), D31.3 (K), D32.3 (K), R32.1, U15.3 (IN+)
SPI0_CSn: U1.7 (GPIO5), U11.1 (~CS)
SPI0_RX: U1.6 (GPIO4), U11.15 (DOUT)
SPI0_SCK: U1.4 (GPIO2), U11.16 (SCLK)
SPI0_TX: U1.5 (GPIO3), U11.14 (DIN)
THROTTLE: C9.1, R7.2, R8.2, U11.10 (IN6)
VSENSE: U10.1, U10.2 (-), U11.7 (IN3)
VSENSE_A: U10.6 (-), U10.7, U11.4 (IN0)
VSENSE_B: U11.5 (IN1), U12.1, U12.2 (-)
VSENSE_C: U11.6 (IN2), U12.6 (-), U12.7
VSENSE_IN: D59.2 (A), D60.1 (K), R12.1, R13.2, R26.1
VSENSE_L: U11.8 (IN4), U16.6 (-), U16.7
V_RAW: C4.1, C5.1, C18.1, C19.1, C20.1, D1.C, D6.3 (K), D19.3 (K), D29.3 (K), D64.1 (A), D64.2 (A), J3.2A (2), J3.2B (2), JP7.1 (A), R12.2

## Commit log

2024-07-12 Imported board into KiCad and made first version of schematic.
2024-07-13 Fixed two errors
2024-07-13 replaced shottky diodes
2024-07-13 Adapted footprint for capacitors.
2024-07-13 Updated schematic pdf
2024-07-13 Detach controller power supply from power section.
2024-07-13 updated pdf
2024-07-13 Added diode and resistors to gate drive for faster switch off
2024-07-13 Typo. Cap_bank_a label still on driver for bank c
2024-07-13 Change to mosfets.
2024-07-13 Updated Shottky footprint
2024-07-14 Added component library
2024-07-14 reverted pcb back to original
2024-07-14 Apparently, this file is needed
2024-07-14 Added isolators for digital I/O
2024-07-14 sceled cap bank pic down.
2024-07-14 small changes in readme
2024-07-14 typo
2024-07-14 centered images
2024-07-14 centering didn't work. Let's try again.
2024-07-14 reversed centering attempt
2024-07-14 Added buffers for analog inputs
2024-07-14 Added few more decoupling capacitors.
2024-07-14 Referenced ovp circuit to v_shunt+ rather than ground.
2024-07-14 Added rotor drag
2024-07-15 Added external spi ADC for current and voltage sense per bridge
2024-07-16 Forgot to add new sheets
2024-07-16 Several updates to analog section
2024-07-16 Further work on a/o current sensing circuits.
2024-07-18 Added datasheets
2024-07-18 Added hall sensor doc
2024-07-20 Added Kicad model for mosfet.
2024-07-20 Changed footprint for Mosfet. Needs more work.
2024-07-20 Some further work on pcb
2024-07-27 First version of PCB layout.
2024-07-29 Feature complete, zero eroors in pcb. Still lot of warnings.
2024-07-30 Added analog Hall inputs and worked away lot of warnings.
2024-07-31 Simplification, high and low side driven together.
2024-07-31 Fixed all warnings.
2024-09-12 Change of plans. Make simple controller for MEG only
2024-10-09 Finished buck converter schematic
2024-10-17 Updated gate drivers.
2024-10-18 Forgot to add some footprints.
2024-10-20 Pretty much complete, but a few things left to do.
